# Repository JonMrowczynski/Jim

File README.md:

# Jim

An inexpensive interdisciplinary platform for affective AI, Jim the robot has the ability to talk, express, and interpret basic human emotions.

The Electronics, Firmware, and Master Control Software subprojects are the components required to operate the first two main functionalities of Jim. 

The Kinect Software subproject is required to operate the third main functionality. An AI is used to interpret the data from the Kinect One sensor to allow Jim to interpret basic human emotions from people's facial expressions.

EDDIE is a later embodiment of Jim.

The Documentation folder contains additional information about Jim/EDDIE if you are interested in learning more.

## Requirements for...

### Electronics

- Any PDF reader to view the PDF of the schematic.

- [Autodesk Eagle](https://www.autodesk.com/products/eagle/free-download) >= 9.5 to modify the schematic, board layout, and/or Gerber files.

### Firmware

#### Software

- [MPLAB X IDE](https://www.microchip.com/mplab/mplab-x-ide) >= 5.25 to modify and develop the firmware.

- MPLAB X IPE >= 5.25 to program the PIC microcontrollers.

  - While installing the IDE, you are presented with the choice of also installed the IPE.
  
  - The versions of MPLAB X IDE and MPLAB X IPE should be the same.
  
#### Hardware

- [PICkit 4 In-Circuit Debugger/Programmer](https://www.microchip.com/developmenttools/ProductDetails/PG164140) to flash the PIC microcontrollers with new firmware.

### Master Control Software

#### Software

- Both [OpenJDK](https://adoptopenjdk.net/) and [OpenJFX](https://gluonhq.com/products/javafx/) >= 11 to run and develop the software.
  - The versions of OpenJDK and OpenJFX should be the same.
  
- [Intellij IDEA](https://www.jetbrains.com/idea/download/) >= 2019.2 (recommended, but not necessary).

#### Hardware 

- [USB to MIDI cable](https://www.amazon.com/HDE-Synthesizer-Microphone-Instrument-Converter/dp/B00D3QFHN8/)

### Kinect Software

#### Software

- [Kinect for Windows SDK 2.0](https://www.microsoft.com/en-us/download/details.aspx?id=44561)

- [Microsoft Visual Studio IDE](https://visualstudio.microsoft.com/) >= 2019

Using the Visual Studio Installer that comes with the IDE... 

- Install the following workloads:

  - .NET desktop development
  
  - Desktop development with C++
  
- Install the following individual components if necessary:

  - .NET framework >= 4.8 SDK
  
  - .NET framework >= 4.8 targeting pack

#### Hardware

- [Microsoft XBox Kinect One Sensor Bar](https://www.amazon.com/Microsoft-Xbox-One-Kinect-Sensor-Renewed/dp/B00YT168WA/)

- [XBox One Kinect Adapter](https://www.amazon.com/Adapter-PartsCrop-Windows-Interactive-Development/dp/B07H9TLNV4/) to connect the Kinect One to a Windows PC.

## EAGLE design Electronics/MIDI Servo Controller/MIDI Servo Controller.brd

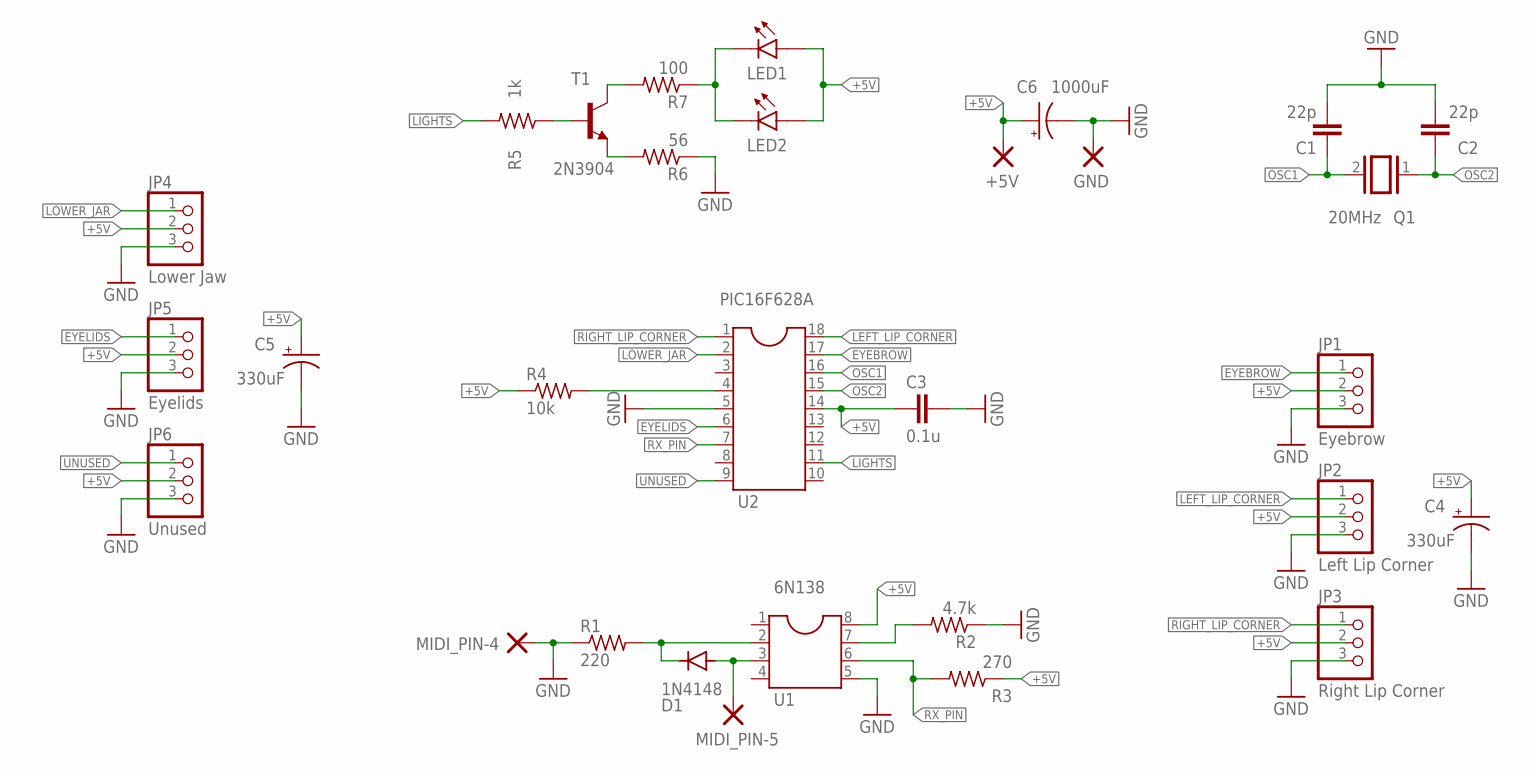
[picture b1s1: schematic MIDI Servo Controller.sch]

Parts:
6N138: U1; SOCKET-08
+5V: DOUBLE_THROUGH_HOLE_PAD
C1, C2: 22p; C050-025X075
C3: 0.1u; C050-025X075
C4, C5: 330uF; E3,5-8
C6: 1000uF; E5-10,5
D1: 1N4148; DO35-10
GND: DOUBLE_THROUGH_HOLE_PAD
JP1: Eyebrow; 1X03
JP2: Left Lip Corner; 1X03
JP3: Right Lip Corner; 1X03
JP4: Lower Jaw; 1X03
JP5: Eyelids; 1X03
JP6: Unused; 1X03
LED1, LED2: REMOTE_LED
MIDI_PIN-4, MIDI_PIN-5: DOUBLE_THROUGH_HOLE_PAD
PIC16F628A: U2; SOCKET-18
Q1: 20MHz; QS
R1: 220; 0207/12
R2: 4.7k; 0207/12
R3: 270; 0207/12
R4: 10k; 0207/12
R5: 1k; 0207/12
R6: 56; 0207/12
R7: 100; 0207/12
T1: 2N3904; TO92

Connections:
+5V: 6N138.8, +5V.P$1, C3.2, C4.+, C5.+, C6.+, JP1.2, JP2.2, JP3.2, JP4.2, JP5.2, JP6.2, LED1.P$1, LED2.P$1, PIC16F628A.14, R3.1, R4.1
EYEBROW: JP1.1, PIC16F628A.17
EYELIDS: JP5.1, PIC16F628A.6
GND: 6N138.5, C1.2, C2.2, C3.1, C4.-, C5.-, C6.-, GND.P$1, JP1.3, JP2.3, JP3.3, JP4.3, JP5.3, JP6.3, MIDI_PIN-4.P$1, PIC16F628A.5, R1.1, R2.1, R6.1
LEFT_LIP_CORNER: JP2.1, PIC16F628A.18
LIGHTS: PIC16F628A.11, R5.2
LOWER_JAR: JP4.1, PIC16F628A.2
MIDI_PIN-5: 6N138.3, D1.A, MIDI_PIN-5.P$1
unnamed: 6N138.2, D1.C, R1.2
unnamed: 6N138.7, R2.2
unnamed: R5.1, T1.2 (B)
unnamed: PIC16F628A.4, R4.2
unnamed: R6.2, T1.3 (E)
unnamed: R7.2, T1.1 (C)
unnamed: LED1.P$2, LED2.P$2, R7.1
OSC1: C1.1, PIC16F628A.16, Q1.2
OSC2: C2.1, PIC16F628A.15, Q1.1
RIGHT_LIP_CORNER: JP3.1, PIC16F628A.1
RX_PIN: 6N138.6, PIC16F628A.7, R3.2
UNUSED: JP6.1, PIC16F628A.9

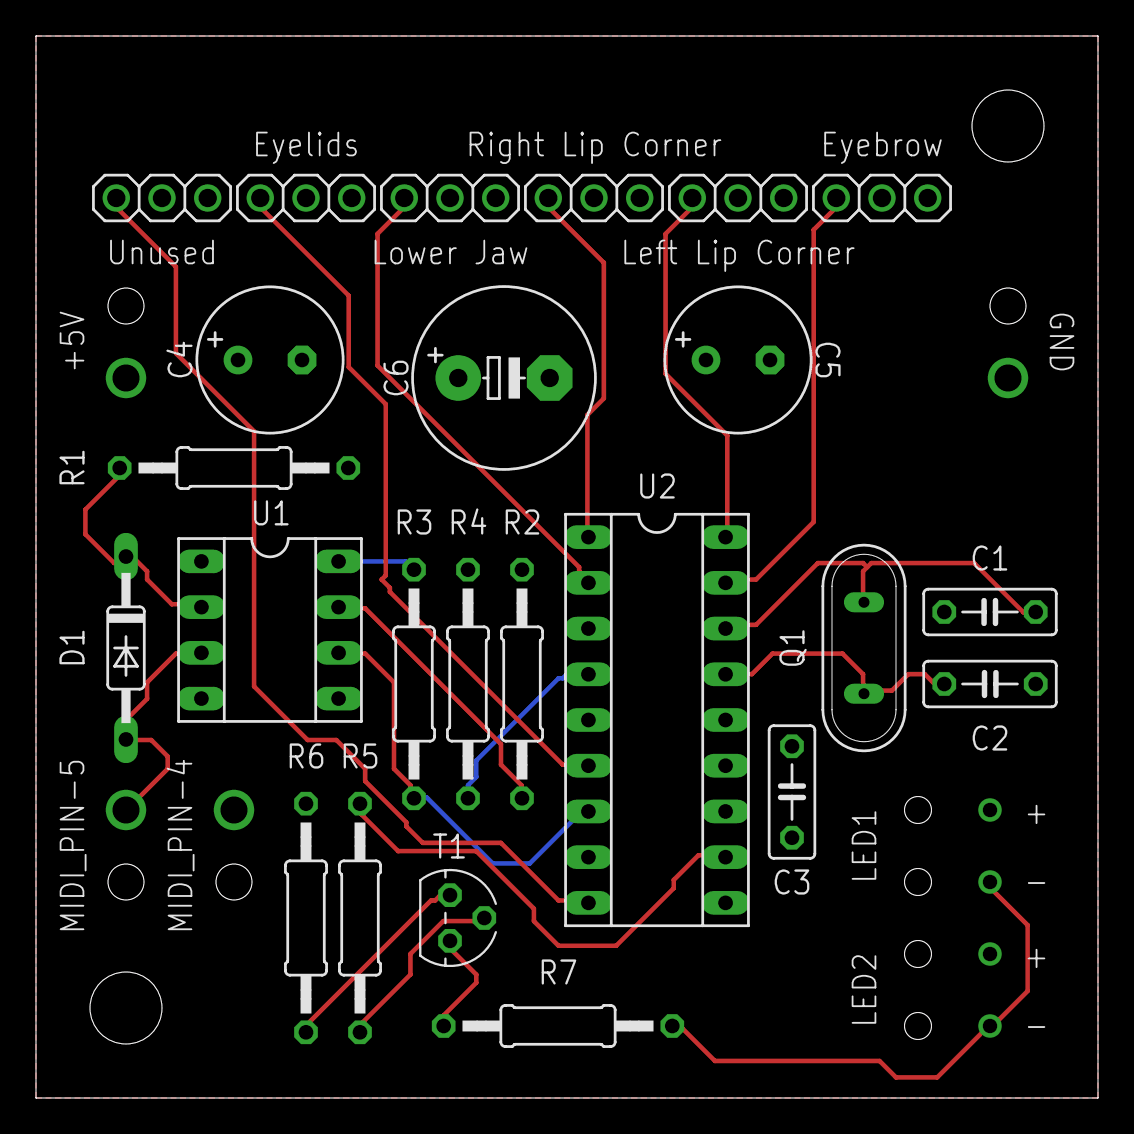
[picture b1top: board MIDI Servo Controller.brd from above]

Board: 2 copper layers, 59.0 x 59.0 mm, 30 parts (0 on the bottom side), 20 nets.

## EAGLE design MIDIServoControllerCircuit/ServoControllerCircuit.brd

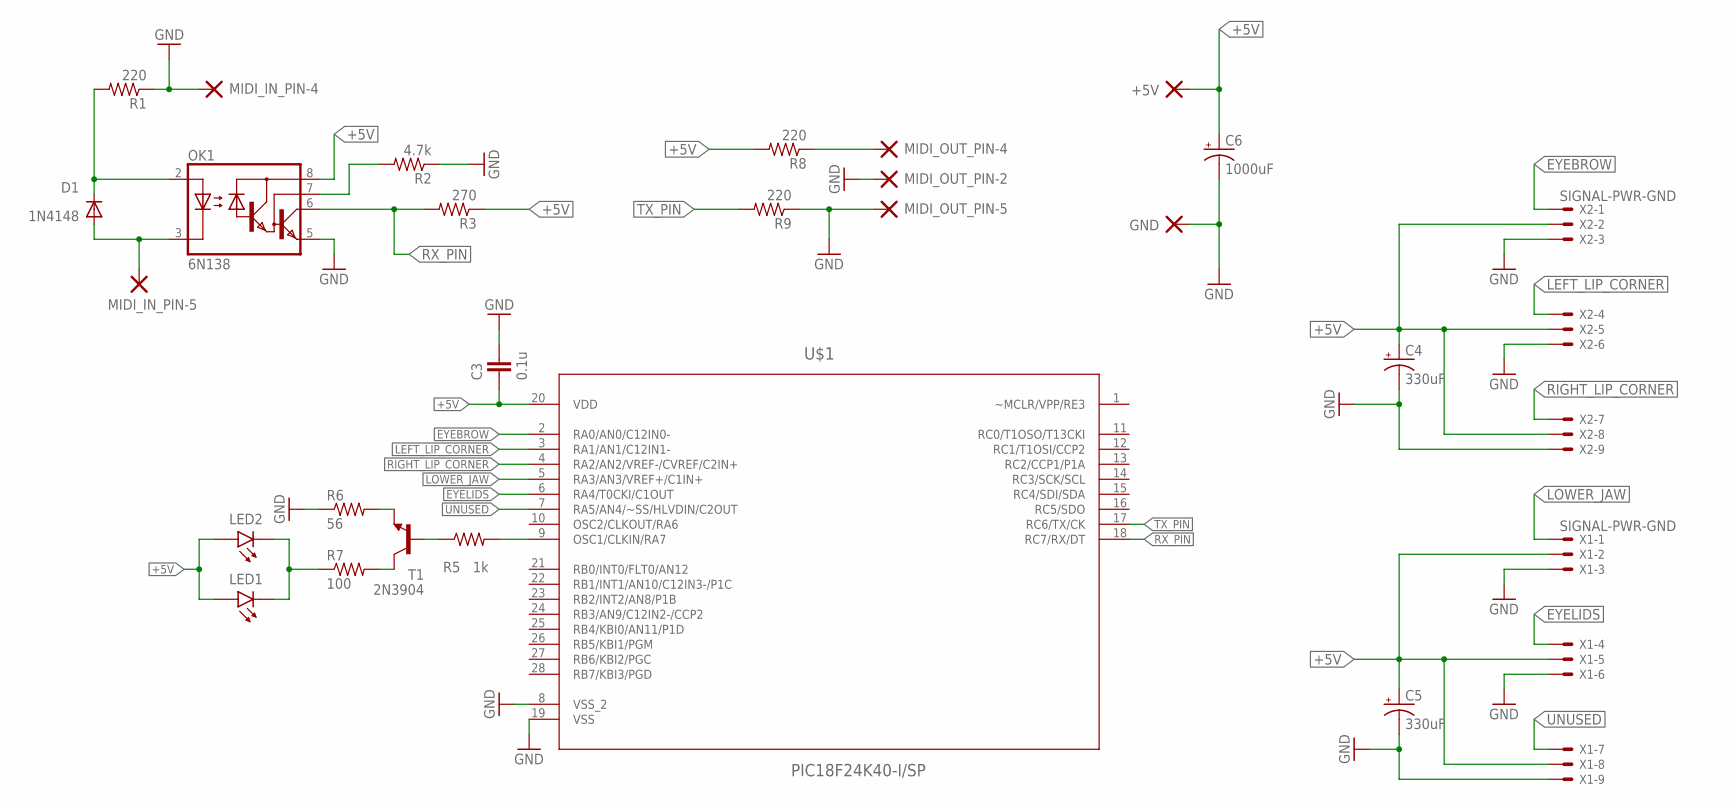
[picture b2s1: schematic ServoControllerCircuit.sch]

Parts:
+5V: DOUBLE_THROUGH_HOLE_PAD
C3: 0.1u; C050-025X075
C4, C5: 330uF; E3,5-8
C6: 1000uF; E5-10,5
D1: 1N4148; DO35-10
GND: DOUBLE_THROUGH_HOLE_PAD
LED1, LED2: REMOTE_LED
MIDI_IN_PIN-4, MIDI_IN_PIN-5: DOUBLE_THROUGH_HOLE_PAD
MIDI_OUT_PIN-2, MIDI_OUT_PIN-4, MIDI_OUT_PIN-5: DOUBLE_THROUGH_HOLE_PAD
OK1: 6N138; DIL08
R1, R8, R9: 220; 0207/12
R2: 4.7k; 0207/12
R3: 270; 0207/12
R5: 1k; 0207/12
R6: 56; 0207/12
R7: 100; 0207/12
T1: 2N3904; TO92
U$1: PIC18F24K40-I/SP; DIP254P762X508-28
X1, X2: SIGNAL-PWR-GND; 22-23-2091

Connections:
+5V: +5V.P$1, C3.2, C4.+, C5.+, C6.+, LED1.P$1, LED2.P$1, OK1.8 (VCC), R3.1, R8.2, U$1.20 (VDD), X1.2, X1.5, X1.8, X2.2, X2.5, X2.8
EYEBROW: U$1.2 (RA0/AN0/C12IN0-), X2.1
EYELIDS: U$1.6 (RA4/T0CKI/C1OUT), X1.4
GND: C3.1, C4.-, C5.-, C6.-, GND.P$1, MIDI_IN_PIN-4.P$1, MIDI_OUT_PIN-2.P$1, MIDI_OUT_PIN-5.P$1, OK1.5 (GND), R1.1, R2.1, R6.1, R9.1, U$1.8 (VSS_2), U$1.19 (VSS), X1.3, X1.6, X1.9, X2.3, X2.6, X2.9
LEFT_LIP_CORNER: U$1.3 (RA1/AN1/C12IN1-), X2.4
LIGHTS: R5.2, U$1.9 (OSC1/CLKIN/RA7)
LOWER_JAW: U$1.5 (RA3/AN3/VREF+/C1IN+), X1.1
MIDI_PIN-5: D1.A, MIDI_IN_PIN-5.P$1, OK1.3 (C)
unnamed: D1.C, OK1.2 (A), R1.2
unnamed: OK1.7 (VB), R2.2
unnamed: R5.1, T1.2 (B)
unnamed: R6.2, T1.3 (E)
unnamed: R7.2, T1.1 (C)
unnamed: LED1.P$2, LED2.P$2, R7.1
unnamed: MIDI_OUT_PIN-4.P$1, R8.1
RIGHT_LIP_CORNER: U$1.4 (RA2/AN2/VREF-/CVREF/C2IN+), X2.7
RX_PIN: OK1.6 (VO), R3.2, U$1.18 (RC7/RX/DT)
TX_PIN: R9.2, U$1.17 (RC6/TX/CK)
UNUSED: U$1.7 (RA5/AN4/~SS/HLVDIN/C2OUT), X1.7

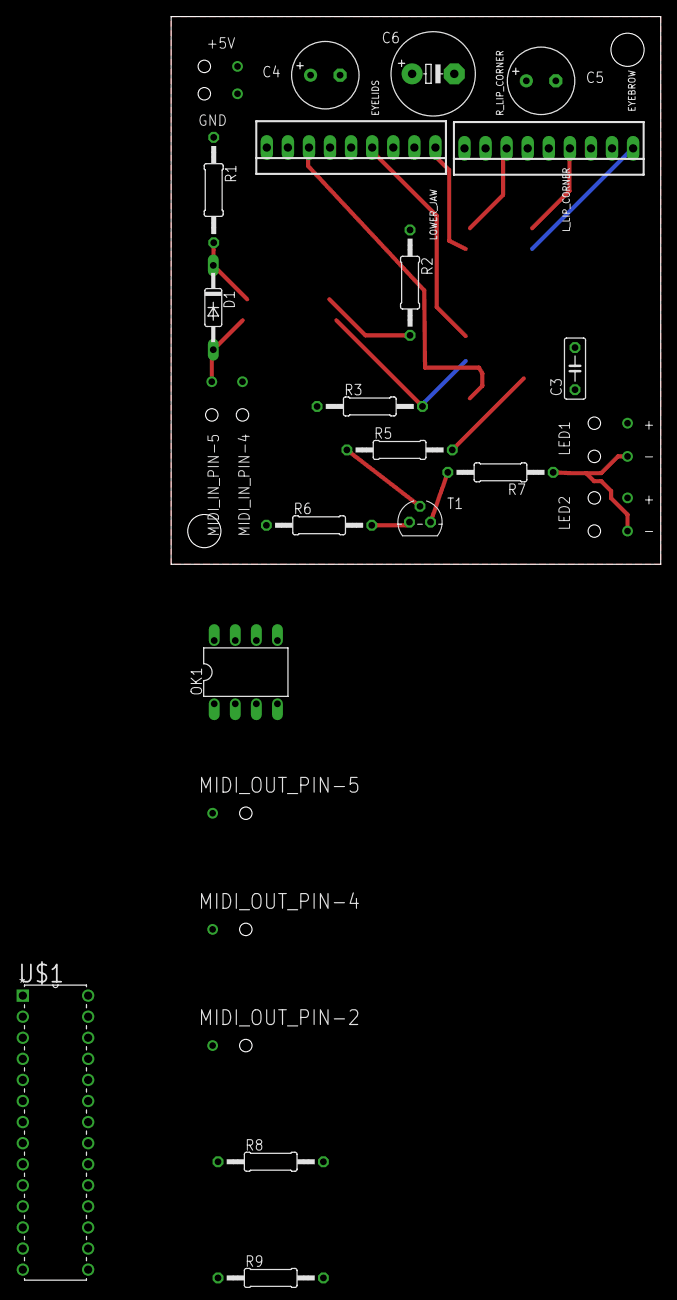
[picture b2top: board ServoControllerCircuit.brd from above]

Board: 2 copper layers, 59.0 x 66.0 mm, 27 parts (0 on the bottom side), 19 nets.

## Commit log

2016-12-13 Updated Jim Firmware
2016-12-13 Uploaded Electronics for Jim
2016-12-13 Uploaded Master Control Software
2016-12-13 Uploaded Kinect Software
2017-09-20 Added files
2017-09-20 restructured file layout
2017-09-20 Updated project
2017-09-20 updated project to later visual studio version
2017-09-20 updated GUI
2018-02-12 Updated MPLAB project stuff
2018-02-18 Modified Board Layout for PCB manufacturing
2018-03-01 Added configuration file
2018-03-01 Some modifications to board and excel spreadsheet
2018-03-01 Removed TX circuitry and moved cost analysis
    Since the TX functionality for the PIC was not tested, I decided to remove it. It is also the case that the cost analysis file for Jim, which is currently in progress, was moved to the Document repos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
2018-03-01 Added Jim Cost analysis
2018-03-01 Renamed directory to better reflect what files represent
2018-03-01 Started Cleaning up Firmware
2018-03-01 Started cleaning up the code and comments
2018-03-03 Cleaned up more of the code and comments
2018-03-03 Finished Cleaning up code and comments
2018-03-03 Fixed Pin mapping
2018-03-03 Renamed PWM outputs to better match what they go to
2018-03-05 Added Double Through Hole Pad and Holes to board
2018-03-05 Removed extra file
2018-03-05 Fixed LED directionality
2018-03-05 Restored board layout
2018-03-05 Added Remote LED component and updated board layout
2018-03-05 Added CAM processor and made Gerber files
2018-03-05 Updated Cost Analysis
2018-03-05 Added Servo Labels to Board Layout
2018-03-05 Added notes
2018-03-13 Added Project Intent
2018-05-28 Updated Circuit for better PIC to compensate for more motor control.
2018-07-24 Cleaned up more of the comments and code.
2018-07-24 Cleaned up as much of the Jim code as meaningful and without overhauling it.
2018-07-29 Took MIDI output and input circuits out, replaced with XBee circuit. Cleaned up schematic.
2018-07-29 Completed Electrical Rule Check
2018-08-04 Updated .gitignore file
2018-08-11 Migrated old firmware over to new microcontroller, IDE, IPE, and Compiler.
    Project builds, but the current firmware won't work properly on the new microcontroller. However, that is okay since it is ready to be modified to work with the new hardware.
2018-08-14 Changed name of file to more accurately represent what will become of the firmware
2018-09-19 Updated EEPROM for new microcontroller
2018-09-19 Cleaned as much as possible without overhauling everything.
2018-10-16 Got rid of unecessary files
2019-02-01 Updated .gitignore
2019-02-01 fixed untracked files
2019-02-01 Updated some of the documentation
2019-08-10 Moved files from Documentation repo into Documentation folder
2019-08-10 Moved files from Electronics repo into Electronics folder
2019-08-10 Moved files from Firmware repo into Firmware folder
2019-08-10 Moved KinectSoftware files into KinectSoftware folder
2019-08-15 Reverting modifications made to Firmware that are ahead of the rest of the project.
2019-08-15 Revert "Completed Electrical Rule Check"
    This reverts commit d8b7c4145ac0e637a6c31ffbb9533202be862925.
2019-08-15 Reversing modifications made to Electronics that are ahread of the rest of the project.
2019-08-15 Reversed modifications made to Electronics that are ahead of the rest of the project.
2019-08-16 Organized required libraries into folder.
2019-08-16 Removed and move documents over to Electronics folder that are related to that topic.
2019-08-16 Cleaned up schematic and board layout.
2019-08-16 Started updating Jim Cost Analysis spreadsheet.
2019-08-17 Updated Jim Cost Analysis. It is less expensive! :D!
2019-08-17 Updated Double Through Hole pad to compensate for higher amperage carrying wires.
2019-08-17 Updated schematic and board layout with updated component library.
2019-08-17 Updated CAM processor and outputed Gerber files for manufacturing PCBs
2019-08-18 Got rid of some documents in Documentation directory that are not needed.
2019-08-18 Updated Jim Report for AI class.
2019-08-18 Removed parts of project that are ahead of the other parts.
2019-08-18 Added Datasheet for PIC16F628A.
2019-08-18 Cleaned up Firmware
2019-08-18 Added .gitignore
2019-08-18 Updated .gitignore.
2019-08-18 Got rid of old eclipse files.
2019-08-19 First cleaning up of the code...still have a decent amount left to do...
2019-08-19 Continuing to clean the code and comments...
2019-08-20 Did some further cleaning of code and comments.
2019-08-20 Modified states data structure from 2D array to Set of ShortMessages.
2019-08-20 Organized java files into packages. Performed further cleaning of code and comments.
2019-08-22 Fixed some runtime bugs and moved JDK version from 8 to 11.
2019-08-25 Partitioned MidiConnection into better logical components.
2019-08-25 Updated .gitignore file.
2019-08-27 Removed unnecessary files.
2019-08-27 Got rid of unnecessary portions of code.
2019-08-27 Removed the need for RuppetUtils class.
2019-08-27 Renamed files that contain data that the Ruppet uses to run its script.
2019-08-27 Cleaned up the rest of the code except for the RuppetTester class.
2019-08-30 Debugged BreathOfLife Application.
2019-08-30 Cleaned up and debugged RuppetTester.
2019-09-01 Got rid of most files that are not necessary to track and renamed project to better represent what it is.
2019-09-01 Renamed project and cleaned yp C# files.
2019-09-01 Updated .NET framework from 4.5 to 4.7.2.
2019-09-01 Cleaned up code and comments. Migrated over to .NET Framework 4.7.2
2019-09-03 Updated copyright notices in the java files.
2019-09-03 Fixed initial copyright date.
2019-09-11 Updated compiler to 2.10.
2019-09-15 Updated schematic by putting subcircuits into groups.
2019-09-15 Corrected USB MidiDevice search requirements in the method's javadoc.
2019-09-17 Finished cleaning up and testing the FaceRecognitionTester project.
2019-09-18 Finished cleaning up, debugging, and improving ProjectEDDIE. Will now rename...
2019-09-18 Removed FaceRecognitionTester since ProjectEDDIE can be used to test to make sure that the Kinect v2 is working instead.
2019-09-18 Renamed ProjectEDDIE to KinectAndFSATester
2019-09-21 Cleaned up KinectAndFSATester further.
2019-09-21 Started cleaning EDDIE_Eyes project.
2019-09-21 Removed the imageSource since it is not used.
2019-09-24 Cleaned up code and comments and simplified data collection algorithms.
2019-09-24 Updated .NET framework from v4.7.2 to v4.8. Finished cleaning up code and comments. Updated copyright.
2019-09-24 Removed KinectAndFSATester since the last KinectEmotionDeterminer has a project to test the Kinect code anyway.
2019-09-24 Cleaned up unnecessary project files.
2019-09-24 Partitioned .gitignore file into separate files to better indicate what files are being specifically ignored in each project.
2019-09-24 Added those files.
2019-09-24 Moved all Kinect sub projects up one directory since all of the other projects were removed.
2019-09-24 Renamed Kinect window.
2019-09-26 Created README
2019-09-26 Added Master Control Software portion of README
2019-09-26 Corrected Electronics porition of README
2019-09-26 Added PDF of schematic.
2019-09-26 Added Kinect Software portion of README.
    Also cleaned up the links to some of the hardware components.
2019-09-26 Cleaned up README
2019-09-26 Cleaned up Documents folder and added Jim illusion video.
2019-09-26 Finished adding all information to README
2019-09-26 Corrected typo in README
2019-09-26 Added license file.
2019-09-26 Added license comments to each code file.
2019-09-26 Cleaned up intro in README
2019-09-29 Updated Kinect Software Requirements
2019-10-11 Cleaned up some of the comments
2019-10-11 Fixed spacing in README.
2019-10-12 Fixed typo in README
2019-12-09 Cleaned up javadocs and implemented "var" keyword.
2019-12-10 Improved exception handling and corresponding javadoc documentation.
2019-12-10 Further implemented Java Streams.
2020-01-17 Cleaned up setNeutral method in Part class.
2020-01-17 Added required Junit 5 testing jars.
2020-01-17 Modified Part and Movable constructors for cleaner implementation.
2020-01-17 Made Ruppet constants public.
2020-01-17 Cleaned up Lights constructor.
2020-01-17 Made Lights constants public.
2020-01-17 Added LightsTest and PartStateTest.
2020-01-18 Made Part distinction more obvious with HardwarePart and SoftwarePart.
2020-01-18 Wrote SoftwarePartTest and started writing HeartTest.
2020-01-19 Added method to UsbMidiConnection to determine if a USB MIDI connection that the program can use exists.
2020-01-19 Moved fileName into SoftwarePart and added getNumberOfTransitions method.
2020-01-19 Got rid of empty line in EmotionTransitionTimes.txt
2020-01-19 Abstracted out SoftwareTest in HeartTest and VoiceTest.
2020-01-19 Changed hardwareParts from a List to a Set.
2020-01-19 Finished writing SoftwarePartTest and VoiceTest.
2020-01-20 Simplified addition of ShutdownHook.
2020-01-20 Cleaned up classes in connections package and modified methods for better testing.
2020-01-20 Simplified exception handling in PartTest methods.
2020-01-20 Added MidiDeviceConnectionTest and UsbMidiConnectionTest.
2020-01-20 Added SequencerConnectionTest.
2020-01-20 Cleaned up Ruppet and Voice class.
2020-01-20 Added RuppetTest.
2020-01-20 Added additional construction condition to HardwarePartState.
2020-01-20 Made HardwarePartState getters in HardwarePart public.
2020-01-20 Cleaned up RuppetTest and HardwarePartStateTest.
2020-01-20 Added public TestHardwarePart.
2020-01-20 Renamed instance member attributes to states in Emotion class.
2020-01-20 Added EmotionTest class.
2022-01-04 Initial addition of 3D printable parts.
2022-10-23 Update README.md
    Fixed type in README.
2023-11-15 Migrated to Gradle project using Java 17 instead of 11.
2023-11-15 Cleaned up some of the comments.
2026-05-25 Made an initial upgrade/cleaning run.
2026-05-25 Refactored RuppetTester graphics into FXML.
2026-05-25 Condensed some of the methods in RuppetTester.
2026-05-25 Fixed unmodifiable collection being modified.
2026-05-25 Moved RuppetTester to controllers and renamed to ManualController.
2026-05-25 Reorganized the files in the parts package more logically.
2026-05-25 Factored out Alerts in UsbMidiConnection.
2026-05-25 Updated jacoco version.
2026-05-25 Fixed HardwarePartTest tests.
2026-05-25 Fixed test comparison between different kinds of objects.
2026-05-25 Performed some simplifications in Ruppet.
